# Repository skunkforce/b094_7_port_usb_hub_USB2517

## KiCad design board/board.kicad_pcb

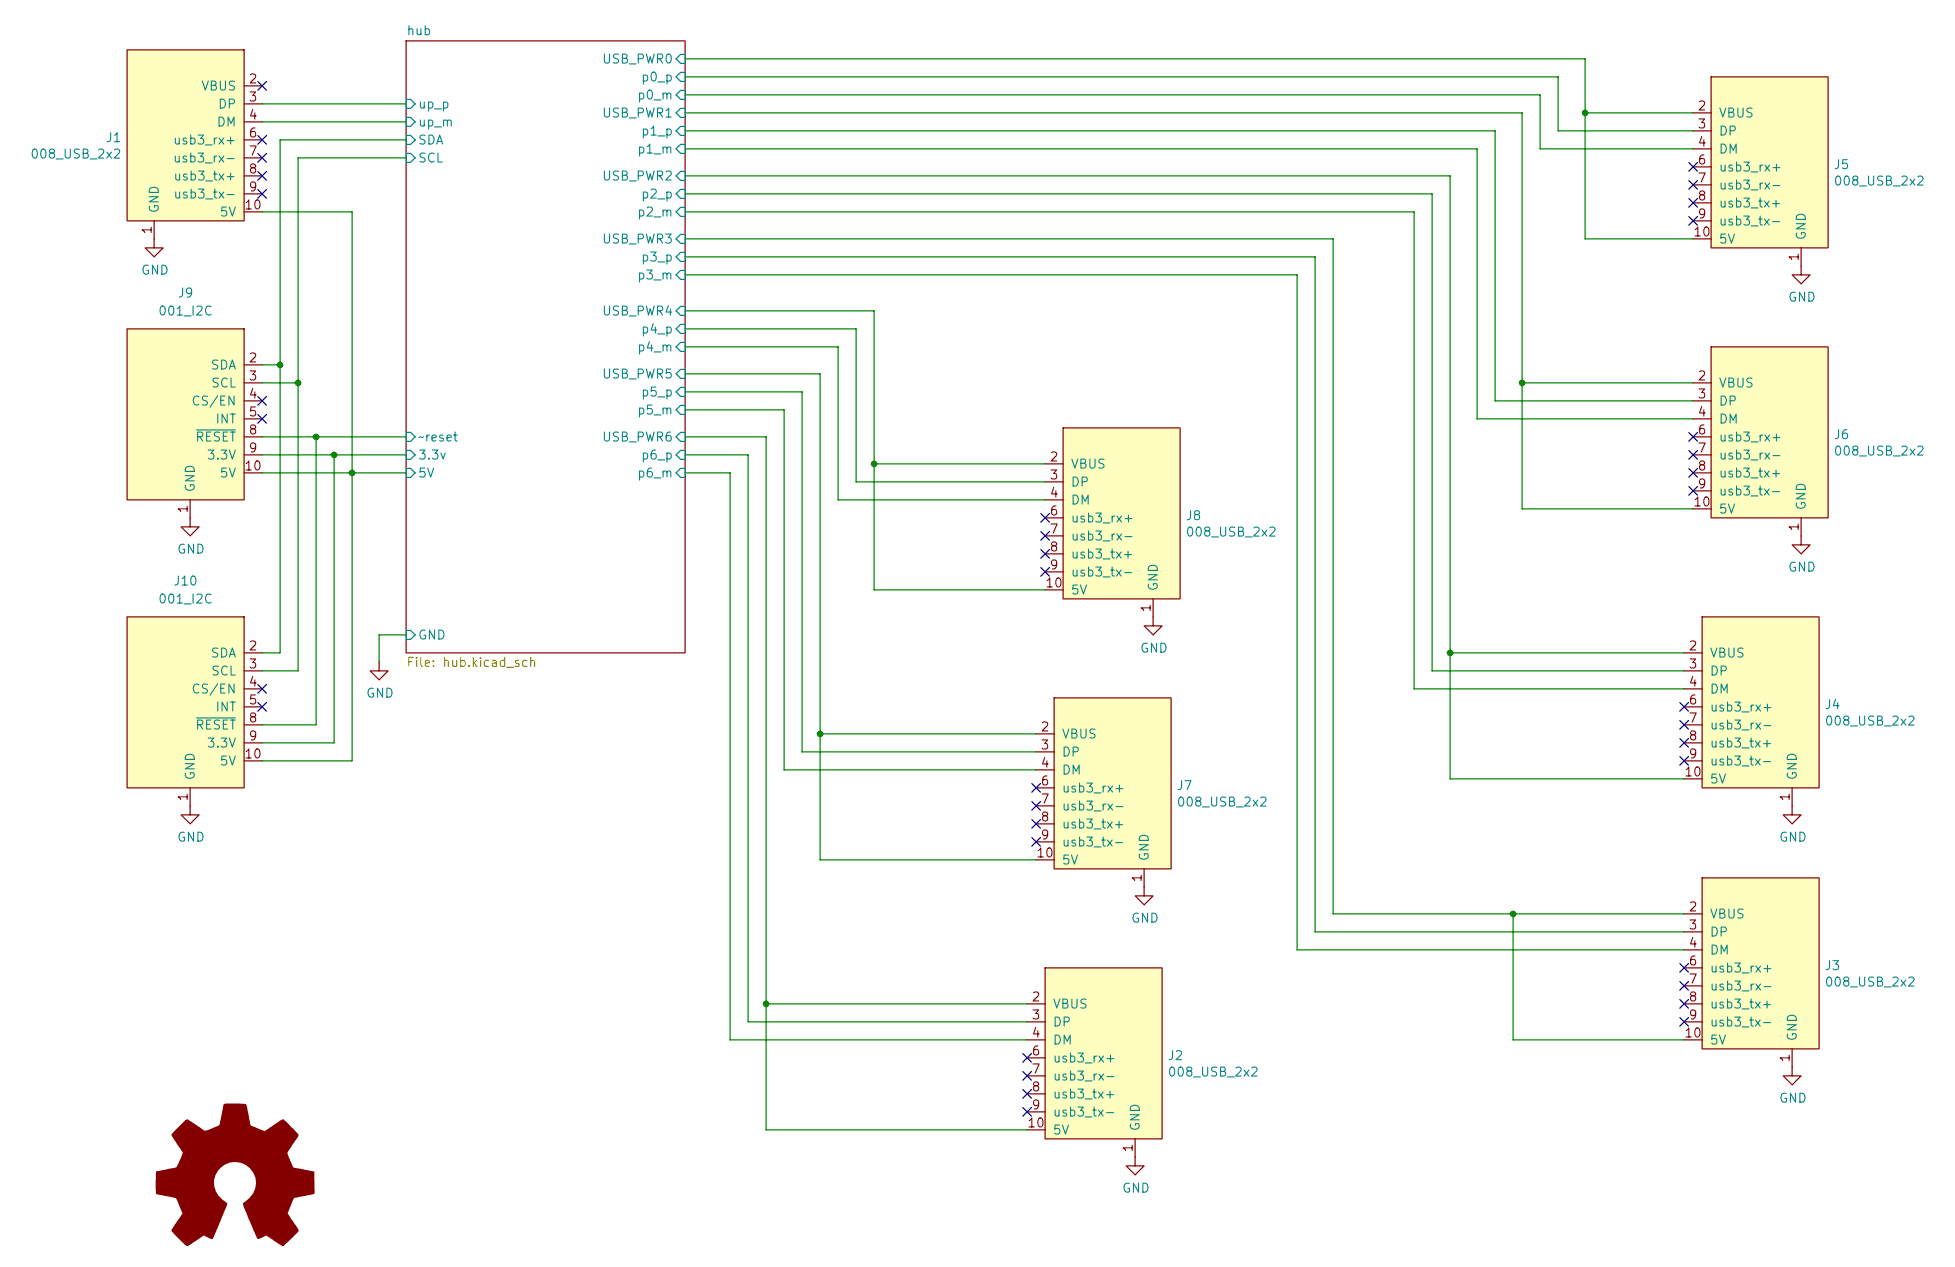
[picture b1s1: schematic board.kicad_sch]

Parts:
J1: 008_USB_2x2; on_edge_2x05_device
J2, J3, J4, J5, J6, J7, J8: 008_USB_2x2; on_edge_2x05_host
J9: 001_I2C; on_edge_2x05_device
J10: 001_I2C; on_edge_2x05_host
l1: Logo_Open_Hardware_Large; OSHW-Logo2_7.3x6mm_SilkScreen

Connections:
/hub/3.3v: J9.9 (3.3V), J10.9 (3.3V); also elsewhere on the board
/hub/5V: J1.10 (5V), J9.10 (5V), J10.10 (5V); also elsewhere on the board
/hub/SCL: J9.3 (SCL), J10.3 (SCL); also elsewhere on the board
/hub/SDA: J9.2 (SDA), J10.2 (SDA); also elsewhere on the board
/hub/USB_PWR0: J5.2 (VBUS), J5.10 (5V); also elsewhere on the board
/hub/USB_PWR1: J6.2 (VBUS), J6.10 (5V); also elsewhere on the board
/hub/USB_PWR2: J4.2 (VBUS), J4.10 (5V); also elsewhere on the board
/hub/USB_PWR3: J3.2 (VBUS), J3.10 (5V); also elsewhere on the board
/hub/USB_PWR4: J8.2 (VBUS), J8.10 (5V); also elsewhere on the board
/hub/USB_PWR5: J7.2 (VBUS), J7.10 (5V); also elsewhere on the board
/hub/USB_PWR6: J2.2 (VBUS), J2.10 (5V); also elsewhere on the board
/hub/p0_m: J5.4 (DM); also elsewhere on the board
/hub/p0_p: J5.3 (DP); also elsewhere on the board
/hub/p1_m: J6.4 (DM); also elsewhere on the board
/hub/p1_p: J6.3 (DP); also elsewhere on the board
/hub/p2_m: J4.4 (DM); also elsewhere on the board
/hub/p2_p: J4.3 (DP); also elsewhere on the board
/hub/p3_m: J3.4 (DM); also elsewhere on the board
/hub/p3_p: J3.3 (DP); also elsewhere on the board
/hub/p4_m: J8.4 (DM); also elsewhere on the board
/hub/p4_p: J8.3 (DP); also elsewhere on the board
/hub/p5_m: J7.4 (DM); also elsewhere on the board
/hub/p5_p: J7.3 (DP); also elsewhere on the board
/hub/p6_m: J2.4 (DM); also elsewhere on the board
/hub/p6_p: J2.3 (DP); also elsewhere on the board
/hub/up_m: J1.4 (DM); also elsewhere on the board
/hub/up_p: J1.3 (DP); also elsewhere on the board
/hub/~reset: J9.8 (~RESET), J10.8 (~RESET); also elsewhere on the board
GND: J1.1 (GND), J2.1 (GND), J3.1 (GND), J4.1 (GND), J5.1 (GND), J6.1 (GND), J7.1 (GND), J8.1 (GND), J9.1 (GND), J10.1 (GND); also elsewhere on the board

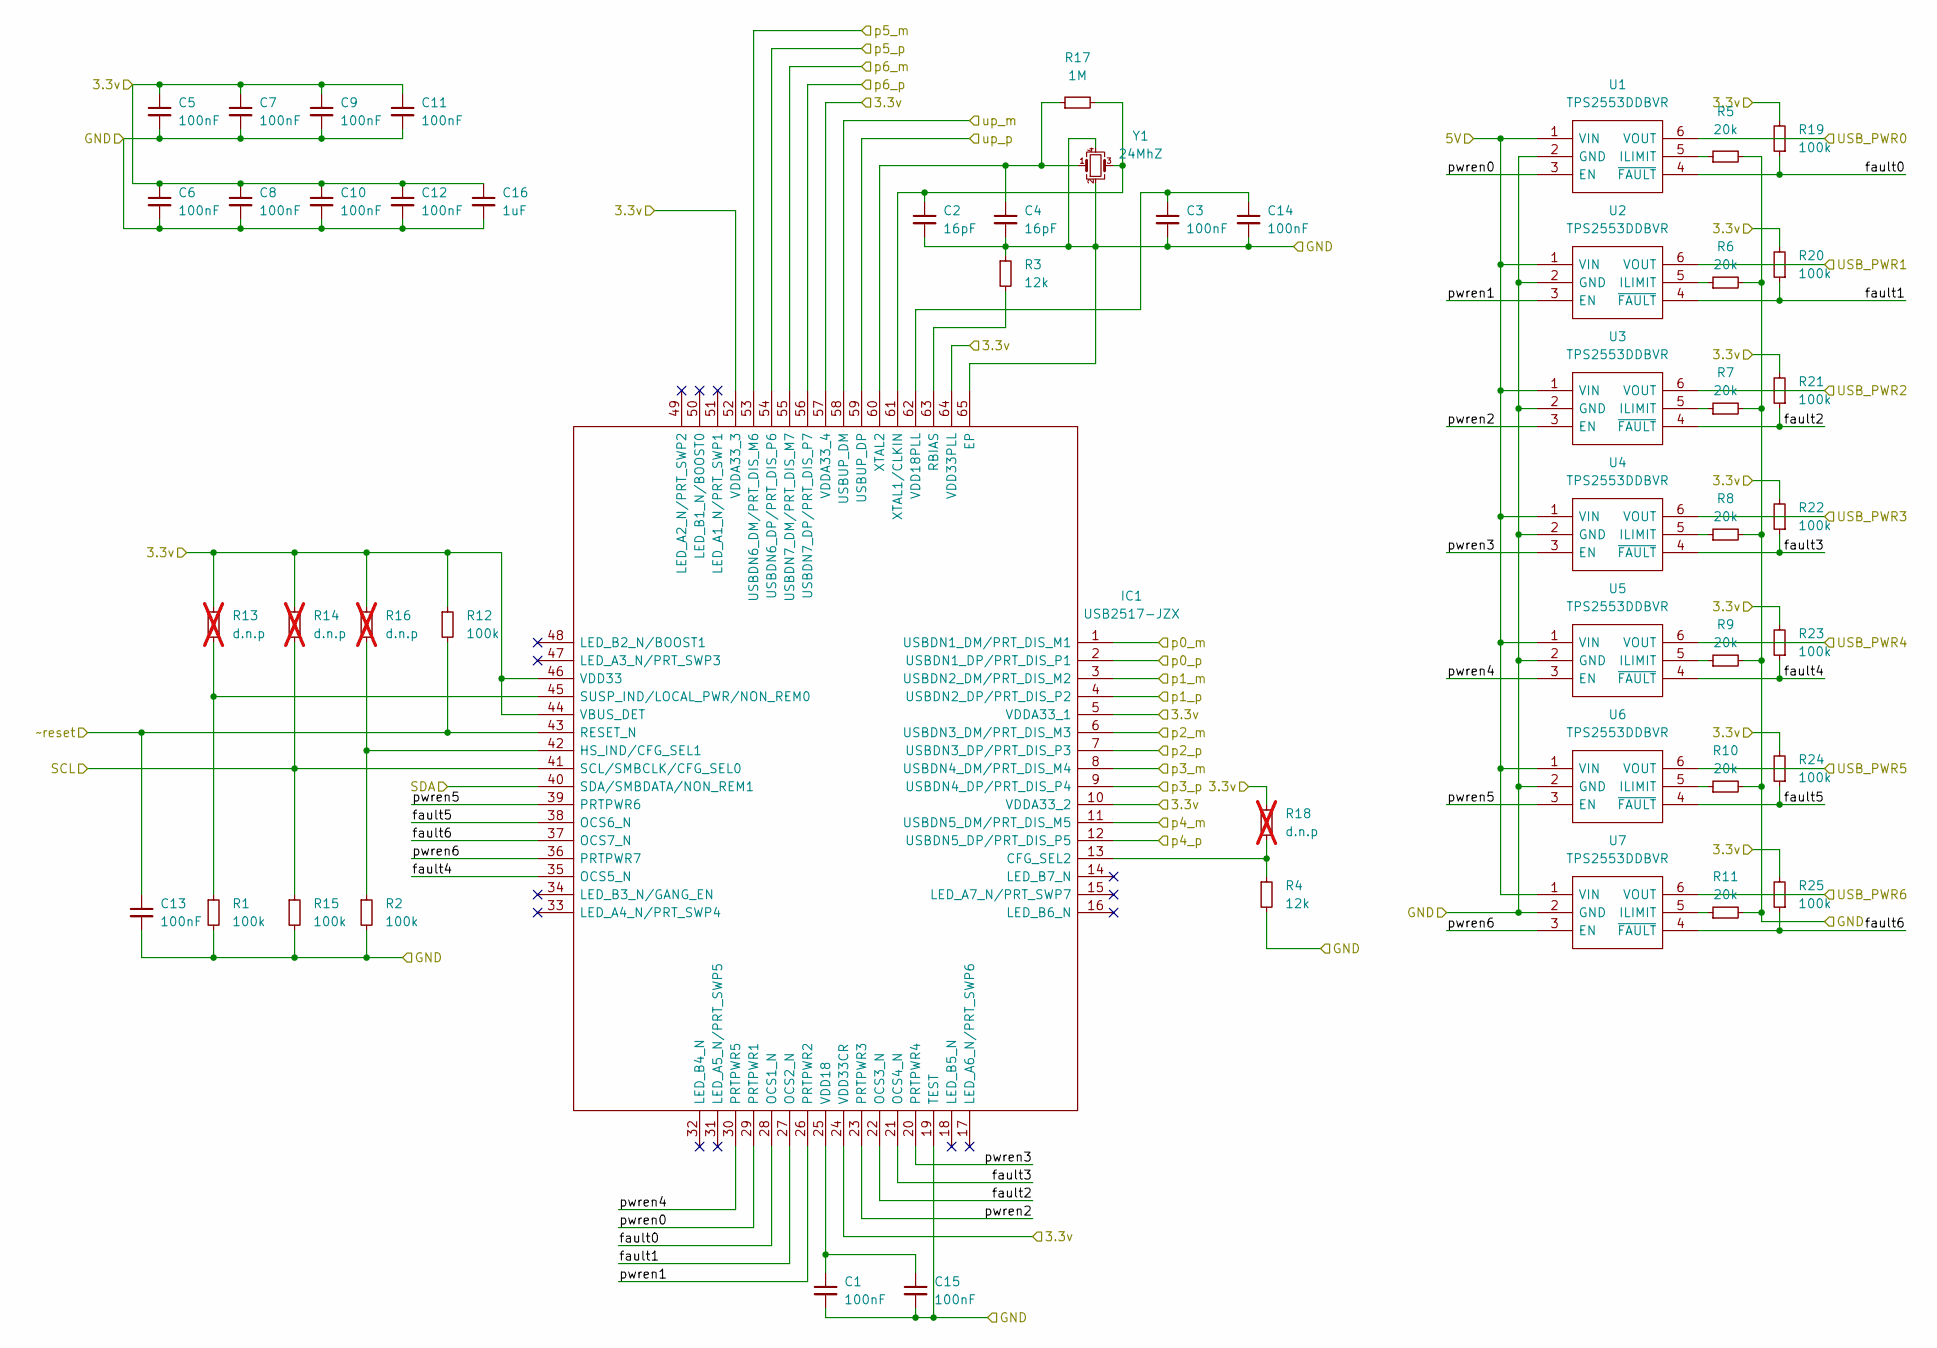
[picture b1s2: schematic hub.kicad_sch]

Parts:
C1, C3, C5, C6, C7, C8, C9, C10, C11, C12, C13, C14, C15: 100nF; C_0402_1005Metric
C2, C4: 16pF; C_0402_1005Metric
C16: 1uF; C_0402_1005Metric
IC1: USB2517-JZX; QFN-64-1EP_9x9mm_P0.5mm_EP4.7x4.7mm; Mouser Part Number 886-USB2517-JZX
R1, R2, R12, R15, R19, R20, R21, R22, R23, R24, R25: 100k; C_0603_1608Metric
R3, R4: 12k; C_0603_1608Metric
R5, R6, R7, R8, R9, R10, R11: 20k; C_0603_1608Metric
R13, R14, R16, R18: d.n.p; C_0603_1608Metric; not fitted
R17: 1M; C_0603_1608Metric
U1, U2, U3, U4, U5, U6, U7: TPS2553DDBVR; TSOP-6_1.65x3.05mm_P0.95mm; MPN TPS2553DDBVR
Y1: 24MhZ; Oscillator_SMD_Abracon_ASE-4Pin_3.2x2.5mm_HandSoldering

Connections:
/hub/3.3v: C5.1, C6.1, C7.1, C8.1, C9.1, C10.1, C11.1, C12.1, C16.1, IC1.5 (VDDA33_1), IC1.10 (VDDA33_2), IC1.24 (VDD33CR), IC1.44 (VBUS_DET), IC1.46 (VDD33), IC1.52 (VDDA33_3), IC1.57 (VDDA33_4), IC1.64 (VDD33PLL), R12.1, R13.1, R14.1, R16.1, R18.1, R19.2, R20.2, R21.2, R22.2, R23.2, R24.2, R25.2; also elsewhere on the board
/hub/5V: U1.1 (VIN), U2.1 (VIN), U3.1 (VIN), U4.1 (VIN), U5.1 (VIN), U6.1 (VIN), U7.1 (VIN); also elsewhere on the board
/hub/SCL: IC1.41 (SCL/SMBCLK/CFG_SEL0), R14.2, R15.1; also elsewhere on the board
/hub/SDA: IC1.40 (SDA/SMBDATA/NON_REM1); also elsewhere on the board
/hub/USB_PWR0: U1.6 (VOUT); also elsewhere on the board
/hub/USB_PWR1: U2.6 (VOUT); also elsewhere on the board
/hub/USB_PWR2: U3.6 (VOUT); also elsewhere on the board
/hub/USB_PWR3: U4.6 (VOUT); also elsewhere on the board
/hub/USB_PWR4: U5.6 (VOUT); also elsewhere on the board
/hub/USB_PWR5: U6.6 (VOUT); also elsewhere on the board
/hub/USB_PWR6: U7.6 (VOUT); also elsewhere on the board
/hub/fault0: IC1.28 (OCS1_N), R19.1, U1.4 (~FAULT)
/hub/fault1: IC1.27 (OCS2_N), R20.1, U2.4 (~FAULT)
/hub/fault2: IC1.22 (OCS3_N), R21.1, U3.4 (~FAULT)
/hub/fault3: IC1.21 (OCS4_N), R22.1, U4.4 (~FAULT)
/hub/fault4: IC1.35 (OCS5_N), R23.1, U5.4 (~FAULT)
/hub/fault5: IC1.38 (OCS6_N), R24.1, U6.4 (~FAULT)
/hub/fault6: IC1.37 (OCS7_N), R25.1, U7.4 (~FAULT)
/hub/p0_m: IC1.1 (USBDN1_DM/PRT_DIS_M1); also elsewhere on the board
/hub/p0_p: IC1.2 (USBDN1_DP/PRT_DIS_P1); also elsewhere on the board
/hub/p1_m: IC1.3 (USBDN2_DM/PRT_DIS_M2); also elsewhere on the board
/hub/p1_p: IC1.4 (USBDN2_DP/PRT_DIS_P2); also elsewhere on the board
/hub/p2_m: IC1.6 (USBDN3_DM/PRT_DIS_M3); also elsewhere on the board
/hub/p2_p: IC1.7 (USBDN3_DP/PRT_DIS_P3); also elsewhere on the board
/hub/p3_m: IC1.8 (USBDN4_DM/PRT_DIS_M4); also elsewhere on the board
/hub/p3_p: IC1.9 (USBDN4_DP/PRT_DIS_P4); also elsewhere on the board
/hub/p4_m: IC1.11 (USBDN5_DM/PRT_DIS_M5); also elsewhere on the board
/hub/p4_p: IC1.12 (USBDN5_DP/PRT_DIS_P5); also elsewhere on the board
/hub/p5_m: IC1.53 (USBDN6_DM/PRT_DIS_M6); also elsewhere on the board
/hub/p5_p: IC1.54 (USBDN6_DP/PRT_DIS_P6); also elsewhere on the board
/hub/p6_m: IC1.55 (USBDN7_DM/PRT_DIS_M7); also elsewhere on the board
/hub/p6_p: IC1.56 (USBDN7_DP/PRT_DIS_P7); also elsewhere on the board
/hub/pwren0: IC1.29 (PRTPWR1), U1.3 (EN)
/hub/pwren1: IC1.26 (PRTPWR2), U2.3 (EN)
/hub/pwren2: IC1.23 (PRTPWR3), U3.3 (EN)
/hub/pwren3: IC1.20 (PRTPWR4), U4.3 (EN)
/hub/pwren4: IC1.30 (PRTPWR5), U5.3 (EN)
/hub/pwren5: IC1.39 (PRTPWR6), U6.3 (EN)
/hub/pwren6: IC1.36 (PRTPWR7), U7.3 (EN)
/hub/up_m: IC1.58 (USBUP_DM); also elsewhere on the board
/hub/up_p: IC1.59 (USBUP_DP); also elsewhere on the board
/hub/~reset: C13.1, IC1.43 (RESET_N), R12.2; also elsewhere on the board
GND: C1.2, C2.2, C3.2, C4.2, C5.2, C6.2, C7.2, C8.2, C9.2, C10.2, C11.2, C12.2, C13.2, C14.2, C15.2, C16.2, IC1.19 (TEST), IC1.65 (EP), R1.2, R2.2, R3.1, R4.2, R5.2, R6.2, R7.2, R8.2, R9.2, R10.2, R11.2, R15.2, U1.2 (GND), U2.2 (GND), U3.2 (GND), U4.2 (GND), U5.2 (GND), U6.2 (GND), U7.2 (GND), Y1.2, Y1.4; also elsewhere on the board
unnamed: IC1.13 (CFG_SEL2), R4.1, R18.2
unnamed: IC1.42 (HS_IND/CFG_SEL1), R2.1, R16.2
unnamed: IC1.63 (RBIAS), R3.2
unnamed: IC1.45 (SUSP_IND/LOCAL_PWR/NON_REM0), R1.1, R13.2
unnamed: C1.1, C15.1, IC1.25 (VDD18)
unnamed: C3.1, C14.1, IC1.62 (VDD18PLL)
unnamed: C2.1, IC1.61 (XTAL1/CLKIN), R17.2, Y1.3
unnamed: C4.1, IC1.60 (XTAL2), R17.1, Y1.1
unnamed: R5.1, U1.5 (ILIMIT)
unnamed: R6.1, U2.5 (ILIMIT)
unnamed: R7.1, U3.5 (ILIMIT)
unnamed: R8.1, U4.5 (ILIMIT)
unnamed: R9.1, U5.5 (ILIMIT)
unnamed: R10.1, U6.5 (ILIMIT)
unnamed: R11.1, U7.5 (ILIMIT)

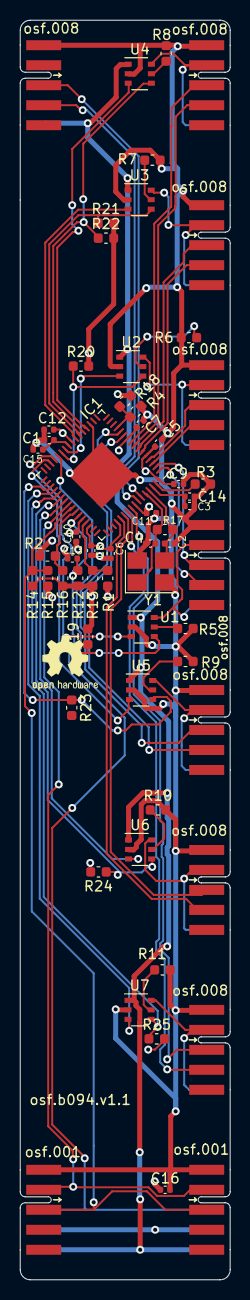
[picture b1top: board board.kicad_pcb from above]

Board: 4 copper layers, 21.0 x 126.0 mm, 61 parts (0 on the bottom side), 58 nets.

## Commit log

2023-12-22 fixed I2C bugs
